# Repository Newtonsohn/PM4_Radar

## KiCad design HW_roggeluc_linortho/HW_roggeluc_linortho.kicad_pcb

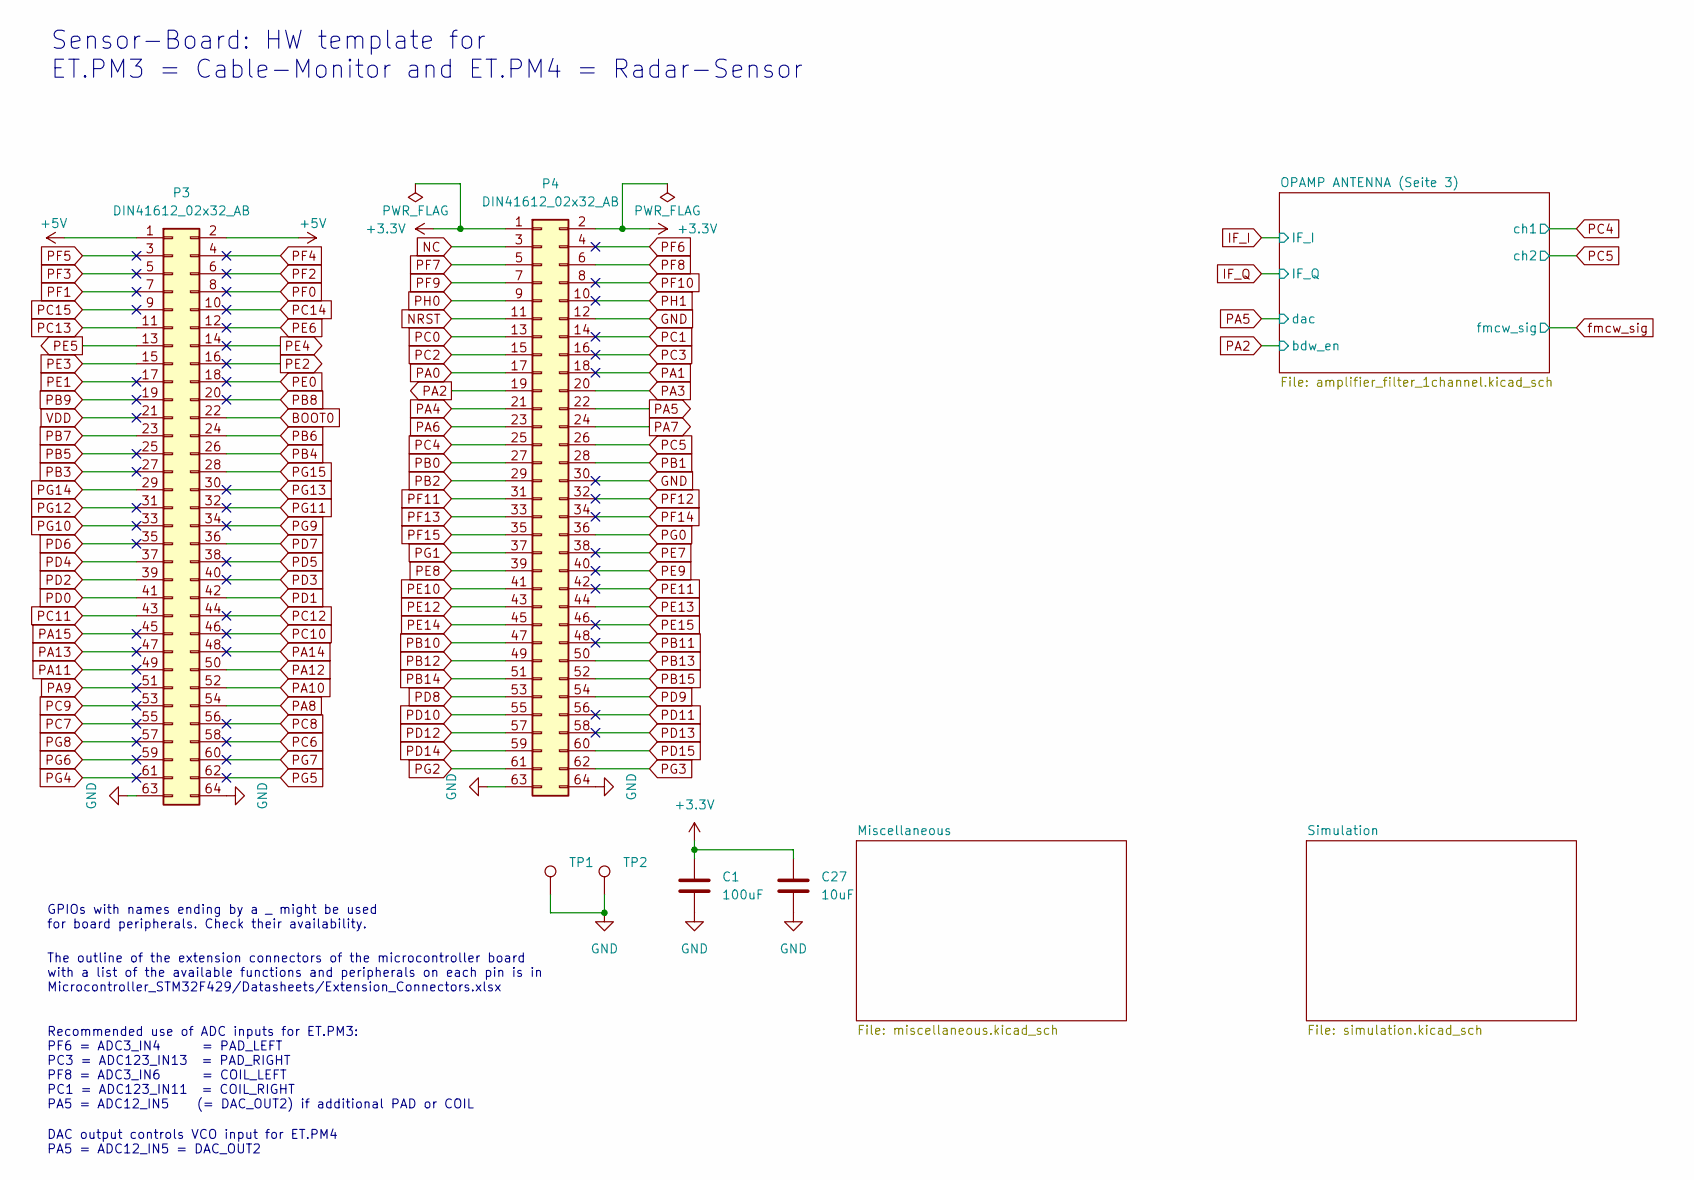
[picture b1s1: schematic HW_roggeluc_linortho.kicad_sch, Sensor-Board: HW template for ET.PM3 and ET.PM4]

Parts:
C1: 100uF; C_0805_2012Metric_Pad1.18x1.45mm_HandSolder
C27: 10uF; C_0805_2012Metric_Pad1.18x1.45mm_HandSolder
P3, P4: DIN41612_02x32_AB; PinSocket_2x32_P2.54mm_Vertical
TP1, TP2: TestPoint_Loop_D2.60mm_Drill1.6mm_Beaded

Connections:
+3.3V: C1.1, C27.1, P4.1 (Pin_a1), P4.2 (Pin_b1); also elsewhere on the board
+5V: P3.1 (Pin_a1), P3.2 (Pin_b1); also elsewhere on the board
BOOT0: P3.22 (Pin_b11)
Enable: P3.27 (Pin_a14); also elsewhere on the board
GND: C1.2, C27.2, P3.63 (Pin_a32), P3.64 (Pin_b32), P4.12 (Pin_b6), P4.30 (Pin_b15), P4.63 (Pin_a32), P4.64 (Pin_b32), TP1.1, TP2.1; also elsewhere on the board
LED_ON: P3.51 (Pin_a26); also elsewhere on the board
NC: P4.3 (Pin_a2)
NRST: P4.11 (Pin_a6)
PA0: P4.17 (Pin_a9)
PA1: P4.18 (Pin_b9)
PA2: P4.19 (Pin_a10); also elsewhere on the board
PA3: P4.20 (Pin_b10)
PA4: P4.21 (Pin_a11)
PA5: P4.22 (Pin_b11); also elsewhere on the board
PA6: P4.23 (Pin_a12); also elsewhere on the board
PA7: P4.24 (Pin_b12)
PA8: P3.54 (Pin_b27); also elsewhere on the board
PA10: P3.52 (Pin_b26)
PA11: P3.49 (Pin_a25)
PA12: P3.50 (Pin_b25)
PA13: P3.47 (Pin_a24)
PA14: P3.48 (Pin_b24)
PA15: P3.45 (Pin_a23)
PB0: P4.27 (Pin_a14)
PB1: P4.28 (Pin_b14)
PB2: P4.29 (Pin_a15)
PB4: P3.26 (Pin_b13)
PB5: P3.25 (Pin_a13)
PB6: P3.24 (Pin_b12)
PB7: P3.23 (Pin_a12)
PB8: P3.20 (Pin_b10)
PB9: P3.19 (Pin_a10)
PB10: P4.47 (Pin_a24)
PB11: P4.48 (Pin_b24)
PB12: P4.49 (Pin_a25)
PB13: P4.50 (Pin_b25)
PB14: P4.51 (Pin_a26)
PB15: P4.52 (Pin_b26)
PC0: P4.13 (Pin_a7)
PC1: P4.14 (Pin_b7)
PC2: P4.15 (Pin_a8)
PC3: P4.16 (Pin_b8)
PC4: P4.25 (Pin_a13); also elsewhere on the board
PC5: P4.26 (Pin_b13); also elsewhere on the board
PC6: P3.58 (Pin_b29)
PC7: P3.55 (Pin_a28)
PC8: P3.56 (Pin_b28)
PC9: P3.53 (Pin_a27)
PC10: P3.46 (Pin_b23)
PC11: P3.43 (Pin_a22)
PC12: P3.44 (Pin_b22)
PC13: P3.11 (Pin_a6)
PC14: P3.10 (Pin_b5)
PC15: P3.9 (Pin_a5)
PD0: P3.41 (Pin_a21)
PD1: P3.42 (Pin_b21)
PD2: P3.39 (Pin_a20)
PD3: P3.40 (Pin_b20)
PD4: P3.37 (Pin_a19)
PD5: P3.38 (Pin_b19)
PD6: P3.35 (Pin_a18)
PD7: P3.36 (Pin_b18)
PD8: P4.53 (Pin_a27)
PD9: P4.54 (Pin_b27)
PD10: P4.55 (Pin_a28)
PD11: P4.56 (Pin_b28)
PD12: P4.57 (Pin_a29)
PD13: P4.58 (Pin_b29)
PD14: P4.59 (Pin_a30)
PD15: P4.60 (Pin_b30)
PE0: P3.18 (Pin_b9)
PE1: P3.17 (Pin_a9)
PE2: P3.16 (Pin_b8); also elsewhere on the board
PE3: P3.15 (Pin_a8)
PE4: P3.14 (Pin_b7); also elsewhere on the board
PE5: P3.13 (Pin_a7); also elsewhere on the board
PE6: P3.12 (Pin_b6); also elsewhere on the board
PE7: P4.38 (Pin_b19)
PE8: P4.39 (Pin_a20)
PE9: P4.40 (Pin_b20)
PE10: P4.41 (Pin_a21)
PE11: P4.42 (Pin_b21)
PE12: P4.43 (Pin_a22)
PE13: P4.44 (Pin_b22)
PE14: P4.45 (Pin_a23)
PE15: P4.46 (Pin_b23)
PF0: P3.8 (Pin_b4)
PF1: P3.7 (Pin_a4)
PF2: P3.6 (Pin_b3)
PF3: P3.5 (Pin_a3)
PF4: P3.4 (Pin_b2)
PF5: P3.3 (Pin_a2)
PF6: P4.4 (Pin_b2)
PF7: P4.5 (Pin_a3)
PF8: P4.6 (Pin_b3)
PF9: P4.7 (Pin_a4)
PF10: P4.8 (Pin_b4)
PF11: P4.31 (Pin_a16)
PF12: P4.32 (Pin_b16)
PF13: P4.33 (Pin_a17)
PF14: P4.34 (Pin_b17)
PF15: P4.35 (Pin_a18)
PG0: P4.36 (Pin_b18)
PG1: P4.37 (Pin_a19)
PG2: P4.61 (Pin_a31)
PG3: P4.62 (Pin_b31)
PG4: P3.61 (Pin_a31)
PG5: P3.62 (Pin_b31)
PG6: P3.59 (Pin_a30)
PG7: P3.60 (Pin_b30)
PG8: P3.57 (Pin_a29)
PG9: P3.34 (Pin_b17)
PG10: P3.33 (Pin_a17)
PG11: P3.32 (Pin_b16)
PG12: P3.31 (Pin_a16)
PG13: P3.30 (Pin_b15)
PG14: P3.29 (Pin_a15)
PG15: P3.28 (Pin_b14)
PH0: P4.9 (Pin_a5)
PH1: P4.10 (Pin_b5)
VDD: P3.21 (Pin_a11)

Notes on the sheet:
The outline of the extension connectors of the microcontroller board with a list of the available functions and peripherals on each pin is in Microcontroller_STM32F429/Datasheets/Extension_Connectors.xlsx
DAC output controls VCO input for ET.PM4 PA5 = ADC12_IN5 = DAC_OUT2
GPIOs with names ending by a _ might be used for board peripherals. Check their availability.
Recommended use of ADC inputs for ET.PM3: PF6 = ADC3_IN4 = PAD_LEFT PC3 = ADC123_IN13 = PAD_RIGHT PF8 = ADC3_IN6 = COIL_LEFT PC1 = ADC123_IN11 = COIL_RIGHT PA5 = ADC12_IN5 (= DAC_OUT2) if additional PAD or COIL
Sensor-Board: HW template for ET.PM3 = Cable-Monitor and ET.PM4 = Radar-Sensor

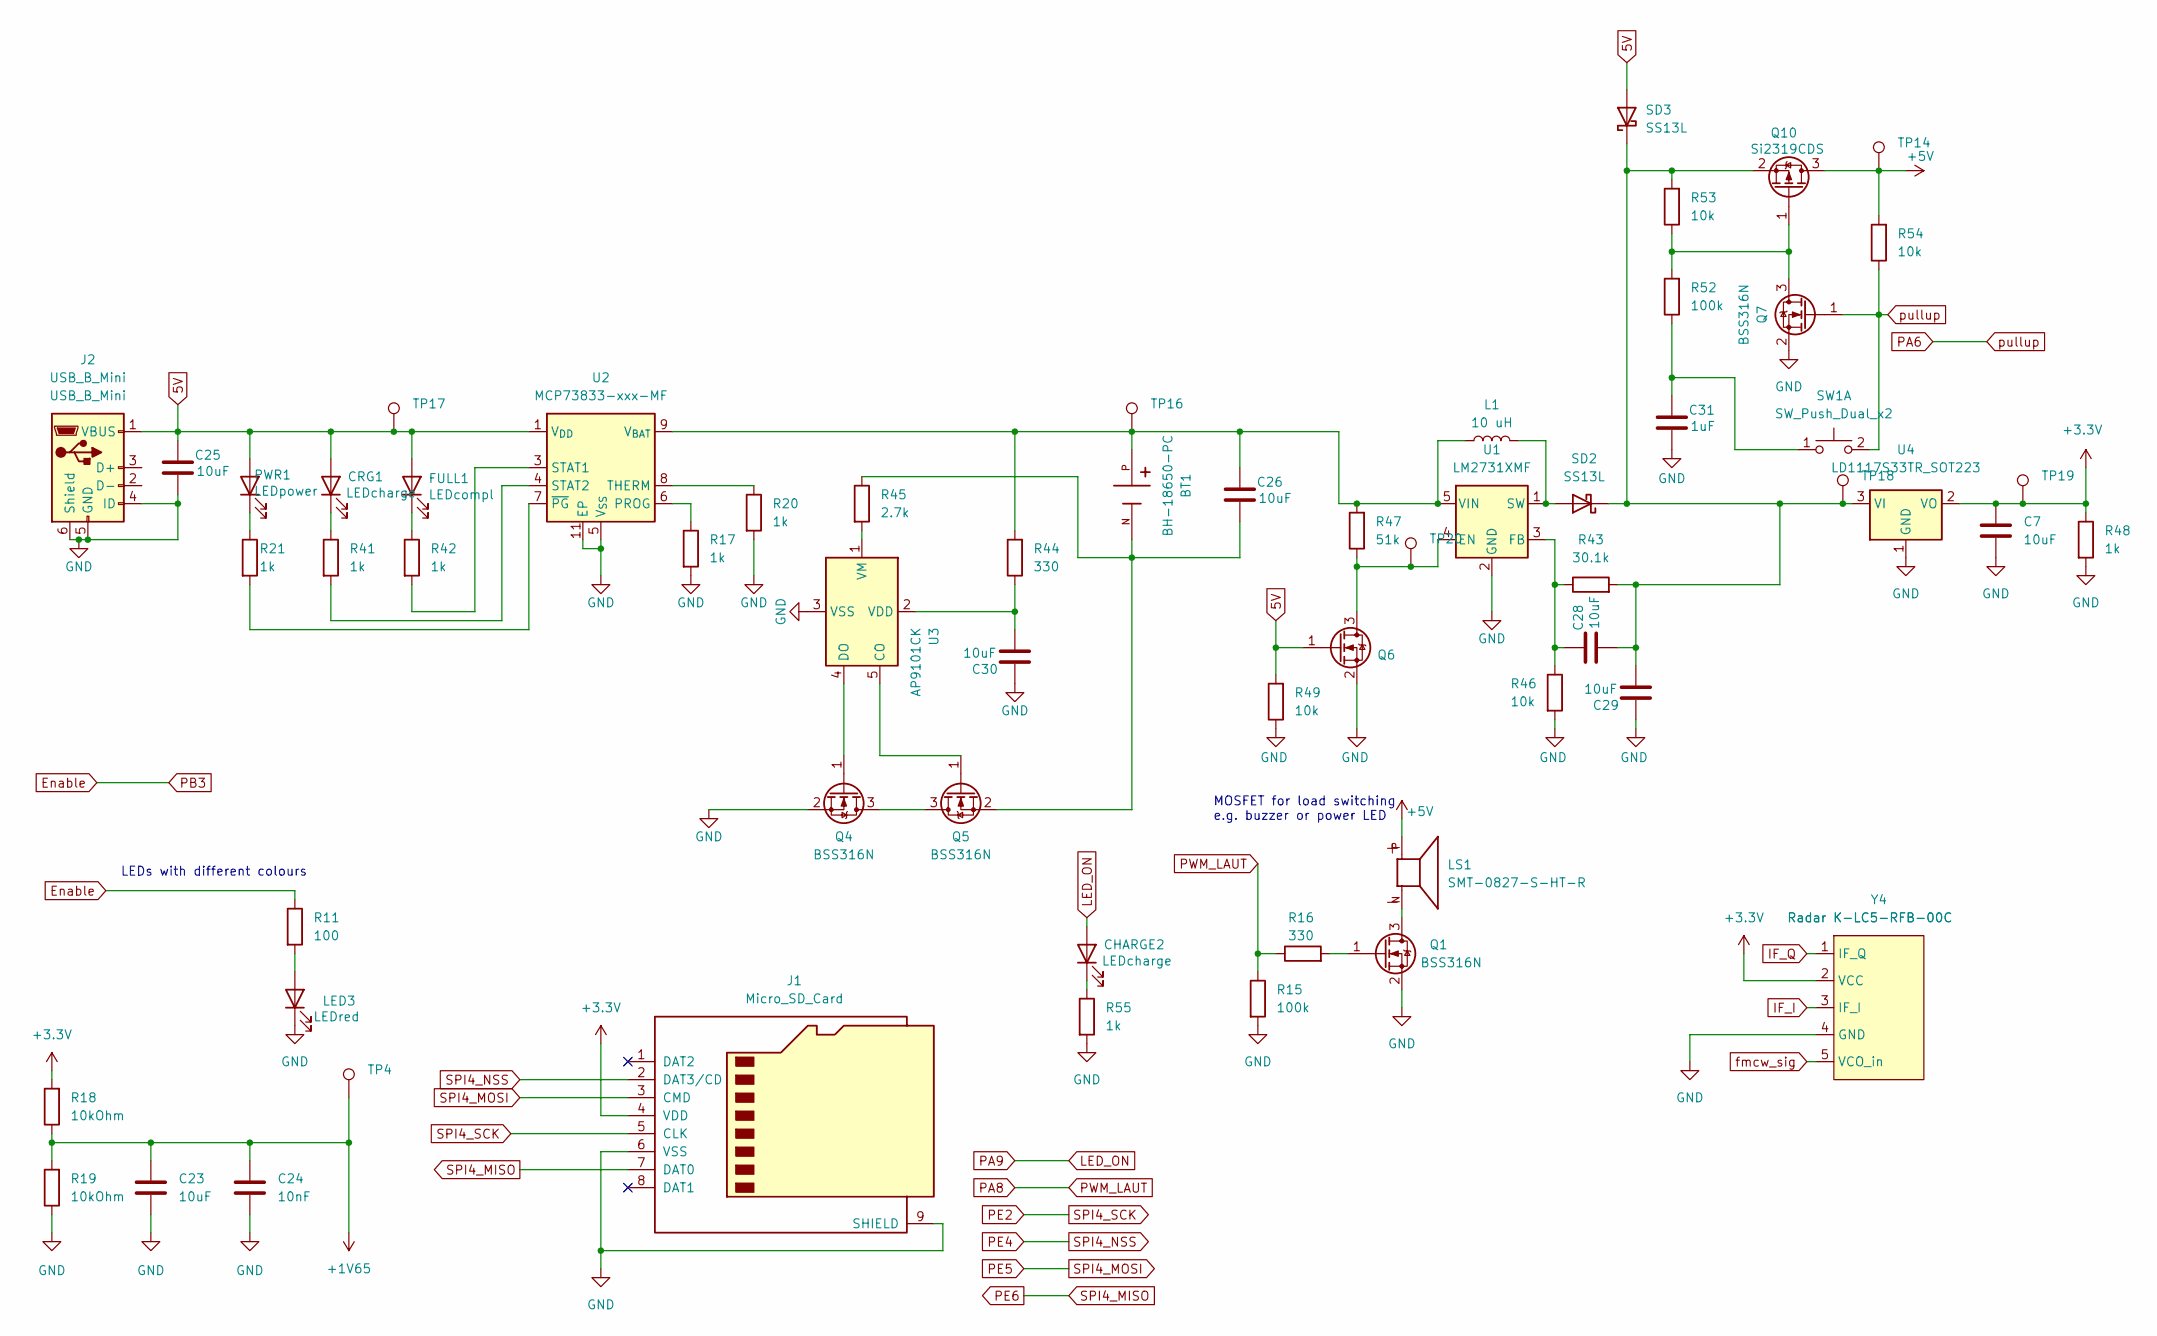
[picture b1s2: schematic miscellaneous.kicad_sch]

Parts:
BT1: BH-18650-PC; BAT_BH-18650-PC; PARTREV 05/17/19
C7, C23, C25, C26, C28, C29, C30: 10uF; C_0805_2012Metric_Pad1.18x1.45mm_HandSolder
C24: 10nF; C_0805_2012Metric_Pad1.18x1.45mm_HandSolder
C31: 1uF; C_0805_2012Metric_Pad1.18x1.45mm_HandSolder
CHARGE2: LEDcharge; LED_1206_3216Metric_Pad1.42x1.75mm_HandSolder
CRG1: LEDcharge; LED_1206_3216Metric_Pad1.42x1.75mm_HandSolder
FULL1: LEDcompl; LED_1206_3216Metric_Pad1.42x1.75mm_HandSolder
J1: Micro_SD_Card; microSD_HC_Wuerth_693072010801
J2: USB_B_Mini; USB_Mini-B_Lumberg_2486_01_Horizontal
L1: 10 uH; L_0805_2012Metric_Pad1.15x1.40mm_HandSolder
LED3: LEDred; LED_1206_3216Metric_Pad1.42x1.75mm_HandSolder
LS1: SMT-0827-S-HT-R; XDCR_SMT-0827-S-HT-R; PARTREV 31/03/20
PWR1: LEDpower; LED_1206_3216Metric_Pad1.42x1.75mm_HandSolder
Q1, Q4, Q5, Q6, Q7: BSS316N; SOT-23
Q10: Si2319CDS; SOT-23
R11: 100; R_0805_2012Metric_Pad1.20x1.40mm_HandSolder
R15, R52: 100k; R_0805_2012Metric_Pad1.20x1.40mm_HandSolder
R16, R44: 330; R_0805_2012Metric_Pad1.20x1.40mm_HandSolder
R17, R20, R21, R41, R42, R48, R55: 1k; R_0805_2012Metric_Pad1.20x1.40mm_HandSolder
R18, R19: 10kOhm; R_0805_2012Metric_Pad1.20x1.40mm_HandSolder
R43: 30.1k; R_0805_2012Metric_Pad1.20x1.40mm_HandSolder
R45: 2.7k; R_0805_2012Metric_Pad1.20x1.40mm_HandSolder
R46, R49, R53, R54: 10k; R_0805_2012Metric_Pad1.20x1.40mm_HandSolder
R47: 51k; R_0805_2012Metric_Pad1.20x1.40mm_HandSolder
SD2, SD3: SS13L; D_SMA
SW1: SW_Push_Dual_x2; SW_SPST_EVQQ2
TP4: TestPoint_Loop_D2.60mm_Drill1.6mm_Beaded
TP14, TP16, TP17, TP18, TP19, TP20: TestPoint_Loop_D2.60mm_Drill1.6mm_Beaded
U1: LM2731XMF; SOT-23-5
U2: MCP73833-xxx-MF; DFN-10-1EP_3x3mm_P0.5mm_EP1.58x2.35mm
U3: AP9101CK; SOT-23-5
U4: LD1117S33TR_SOT223; SOT-223-3_TabPin2
Y4: Radar K-LC5-RFB-00C; Radar_K-LC5

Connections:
5V: C25.1, CRG1.2 (A), FULL1.2 (A), J2.1 (VBUS), PWR1.2 (A), Q6.1 (G), R49.2, SD3.2 (A), TP17.1, U2.1 (V_{DD}), U2.2 (V_{DD})
+1V65: C23.1, C24.1, R18.1, R19.2, TP4.1; also elsewhere on the board
+3.3V: C7.1, J1.4 (VDD), R18.2, R48.1, TP19.1, U4.2 (VO), Y4.2 (VCC); also elsewhere on the board
+5V: LS1.P, Q10.3 (D), R54.2, TP14.1; also elsewhere on the board
Enable: R11.1; also elsewhere on the board
GND: C7.2, C23.2, C24.2, C25.2, C29.1, C30.1, C31.2, J1.6 (VSS), J1.9 (SHIELD), J2.4 (ID), J2.5 (GND), J2.6 (Shield), LED3.1 (K), Q1.2 (S), Q4.2 (S), Q6.2 (S), Q7.2 (S), R15.2, R17.2, R19.1, R20.2, R46.2, R48.2, R49.1, R55.2, U1.2 (GND), U2.5 (V_{SS}), U2.11 (EP), U3.3 (VSS), U4.1 (GND), Y4.4 (GND); also elsewhere on the board
IF_I: Y4.3 (IF_I); also elsewhere on the board
IF_Q: Y4.1 (IF_Q); also elsewhere on the board
LED_ON: CHARGE2.2 (A); also elsewhere on the board
unnamed: CHARGE2.1 (K), R55.1
unnamed: CRG1.1 (K), R41.1
unnamed: FULL1.1 (K), R42.1
unnamed: LED3.2 (A), R11.2
unnamed: PWR1.1 (K), R21.1
unnamed 21: LS1.N, Q1.3 (D); also elsewhere on the board
unnamed: Q1.1 (G), R16.2
unnamed: Q4.3 (D), Q5.3 (D)
unnamed: Q4.1 (G), U3.4 (DO)
unnamed: Q5.1 (G), U3.5 (CO)
unnamed: BT1.N, C26.2, Q5.2 (S), R45.1
unnamed: Q6.3 (D), R47.1, TP20.1, U1.4 (EN)
unnamed: Q7.3 (D), Q10.1 (G), R52.2, R53.1
unnamed: C28.2, C29.2, Q10.2 (S), R43.2, R53.2, SD2.1 (K), SD3.1 (K), TP18.1, U4.3 (VI)
unnamed: L1.2, SD2.2 (A), U1.1 (SW)
unnamed: C31.1, R52.1, SW1.1 (C)
unnamed: C28.1, R43.1, R46.1, U1.3 (FB)
unnamed: BT1.P, C26.1, L1.1, R44.2, R47.2, TP16.1, U1.5 (VIN), U2.9 (V_{BAT}), U2.10 (V_{BAT})
unnamed: R17.1, U2.6 (PROG)
unnamed: R42.2, U2.3 (STAT1)
unnamed: R41.2, U2.4 (STAT2)
unnamed: R20.1, U2.8 (THERM)
unnamed: R21.2, U2.7 (~PG)
unnamed: C30.2, R44.1, U3.2 (VDD)
unnamed: R45.2, U3.1 (VM)
PA6: Q7.1 (G), R54.1, SW1.2 (D); also elsewhere on the board
PA8: R15.1, R16.1; also elsewhere on the board
PE2: J1.5 (CLK); also elsewhere on the board
PE4: J1.2 (DAT3/CD); also elsewhere on the board
PE5: J1.3 (CMD); also elsewhere on the board
PE6: J1.7 (DAT0); also elsewhere on the board
fmcw_sig: Y4.5 (VCO_in); also elsewhere on the board

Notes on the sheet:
MOSFET for load switching e.g. buzzer or power LED
LEDs with different colours

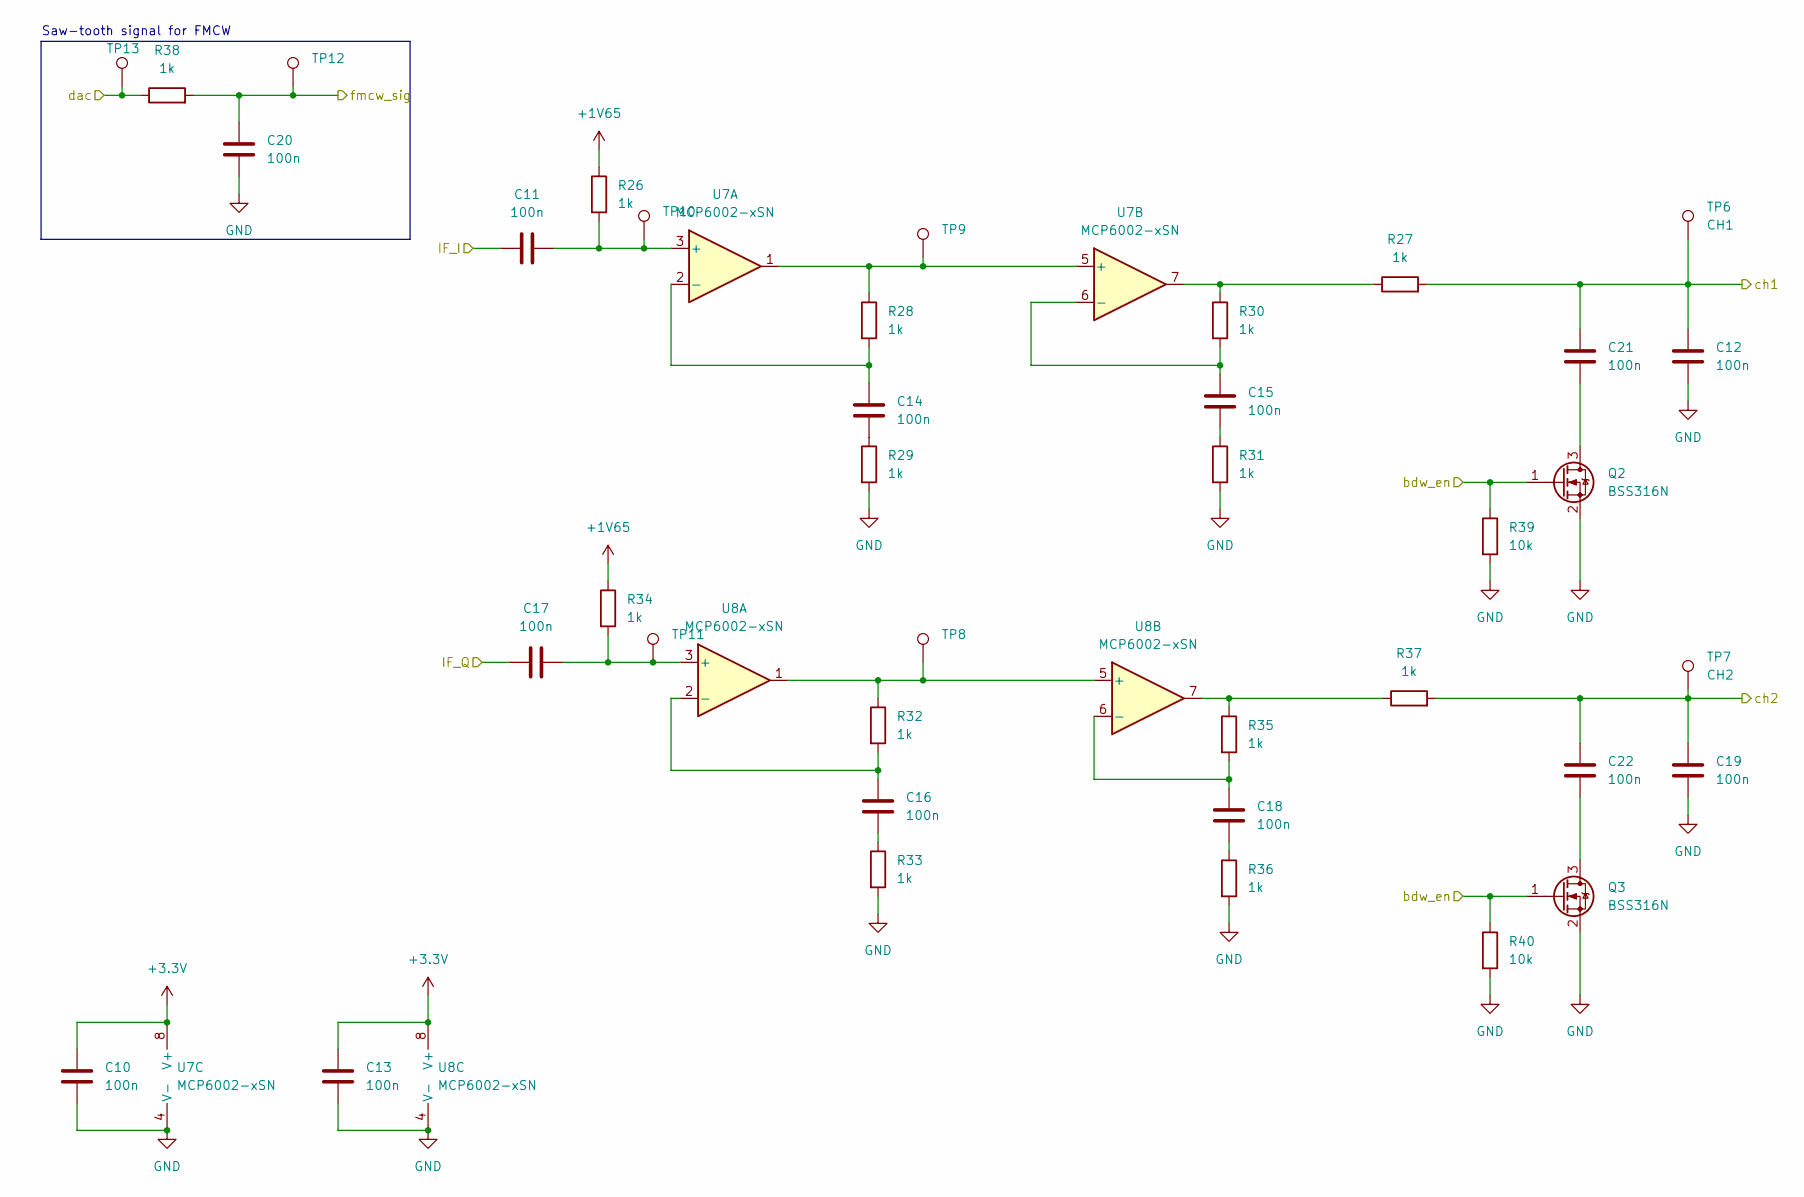
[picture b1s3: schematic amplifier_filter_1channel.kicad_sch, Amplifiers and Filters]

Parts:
C10, C11, C12, C13, C14, C15, C16, C17, C18, C19, C20, C21, C22: 100n; C_0805_2012Metric_Pad1.18x1.45mm_HandSolder
Q2, Q3: BSS316N; SOT-23
R26, R27, R28, R29, R30, R31, R32, R33, R34, R35, R36, R37, R38: 1k; R_0805_2012Metric_Pad1.20x1.40mm_HandSolder
R39, R40: 10k; R_0805_2012Metric_Pad1.20x1.40mm_HandSolder
TP6: CH1; TestPoint_Loop_D2.60mm_Drill1.6mm_Beaded
TP7: CH2; TestPoint_Loop_D2.60mm_Drill1.6mm_Beaded
TP8, TP9, TP10, TP11, TP12, TP13: TestPoint_Loop_D2.60mm_Drill1.6mm_Beaded
U7, U8: MCP6002-xSN; SOIC-8_3.9x4.9mm_P1.27mm

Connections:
+1V65: R26.1, R34.1; also elsewhere on the board
+3.3V: C10.1, C13.1, U7.8 (V+), U8.8 (V+); also elsewhere on the board
GND: C10.2, C12.1, C13.2, C19.1, C20.1, Q2.2 (S), Q3.2 (S), R29.2, R31.2, R33.2, R36.2, R39.2, R40.2, U7.4 (V-), U8.4 (V-); also elsewhere on the board
IF_I: C11.1; also elsewhere on the board
IF_Q: C17.1; also elsewhere on the board
unnamed: C14.1, R29.1
unnamed: C15.1, R31.1
unnamed: C16.1, R33.1
unnamed: C18.1, R36.1
unnamed: C21.1, Q2.3 (D)
unnamed: C22.1, Q3.3 (D)
unnamed: R27.1, R30.1, U7.7
unnamed: R35.1, R37.1, U8.7
unnamed: C11.2, R26.2, TP10.1, U7.3 (+)
unnamed: C14.2, R28.2, U7.2 (-)
unnamed: R28.1, TP9.1, U7.1, U7.5 (+)
unnamed: C15.2, R30.2, U7.6 (-)
unnamed: C17.2, R34.2, TP11.1, U8.3 (+)
unnamed: C16.2, R32.2, U8.2 (-)
unnamed: R32.1, TP8.1, U8.1, U8.5 (+)
unnamed: C18.2, R35.2, U8.6 (-)
PA2: Q2.1 (G), Q3.1 (G), R39.1, R40.1; also elsewhere on the board
PA5: R38.1, TP13.1; also elsewhere on the board
PC4: C12.2, C21.2, R27.2, TP6.1; also elsewhere on the board
PC5: C19.2, C22.2, R37.2, TP7.1; also elsewhere on the board
fmcw_sig: C20.2, R38.2, TP12.1; also elsewhere on the board

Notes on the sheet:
Saw-tooth signal for FMCW

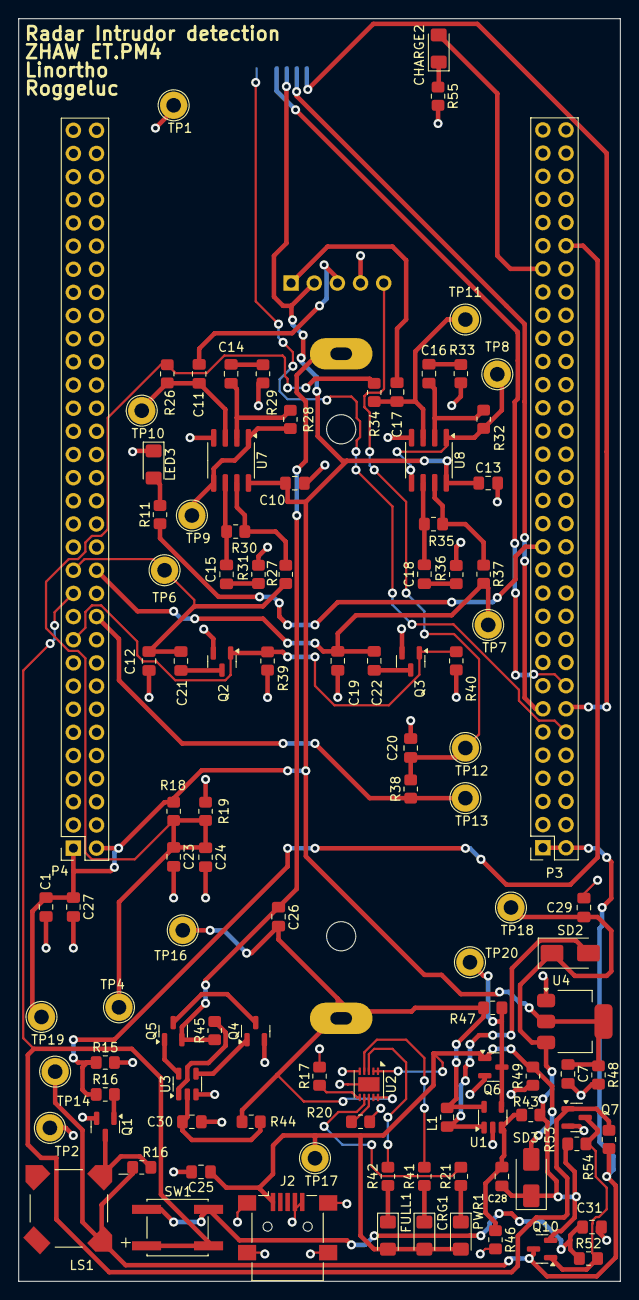
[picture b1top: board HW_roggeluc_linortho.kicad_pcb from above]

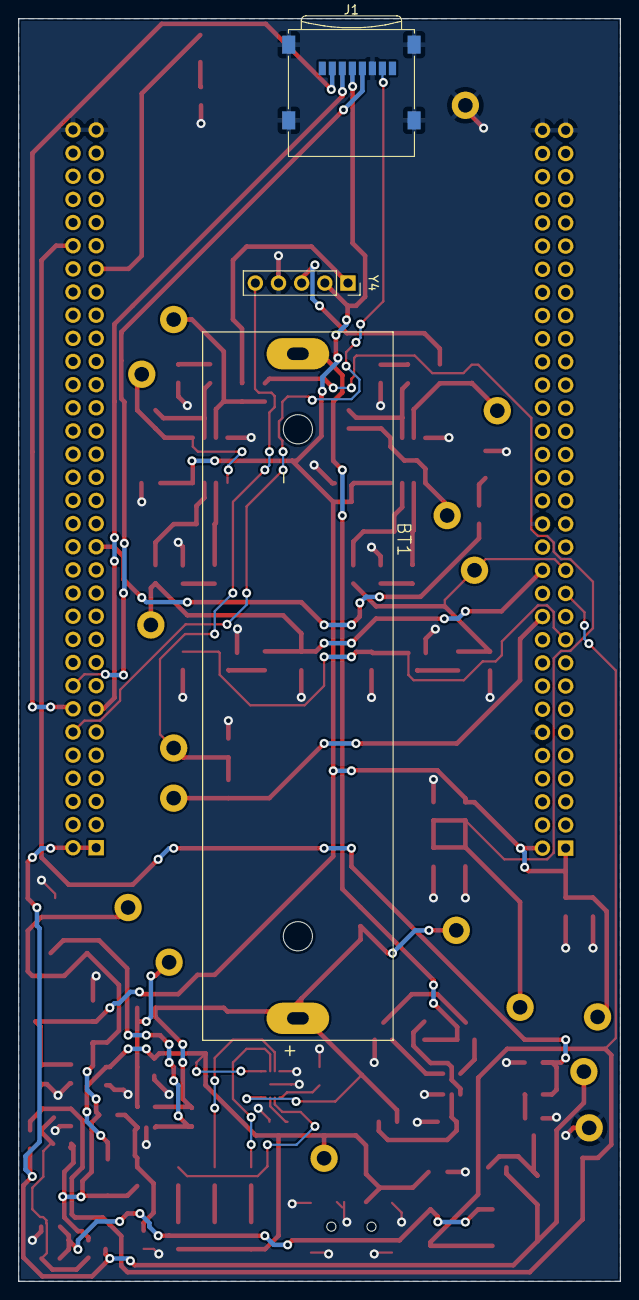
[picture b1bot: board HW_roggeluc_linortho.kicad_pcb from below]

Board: 2 copper layers, 66.0 x 138.5 mm, 108 parts (3 on the bottom side), 61 nets.

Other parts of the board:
R16#2: 10; R_0805_2012Metric_Pad1.20x1.40mm_HandSolder

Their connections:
+5V: R16#2.1; also elsewhere on the board
unnamed 21: R16#2.2; also elsewhere on the board

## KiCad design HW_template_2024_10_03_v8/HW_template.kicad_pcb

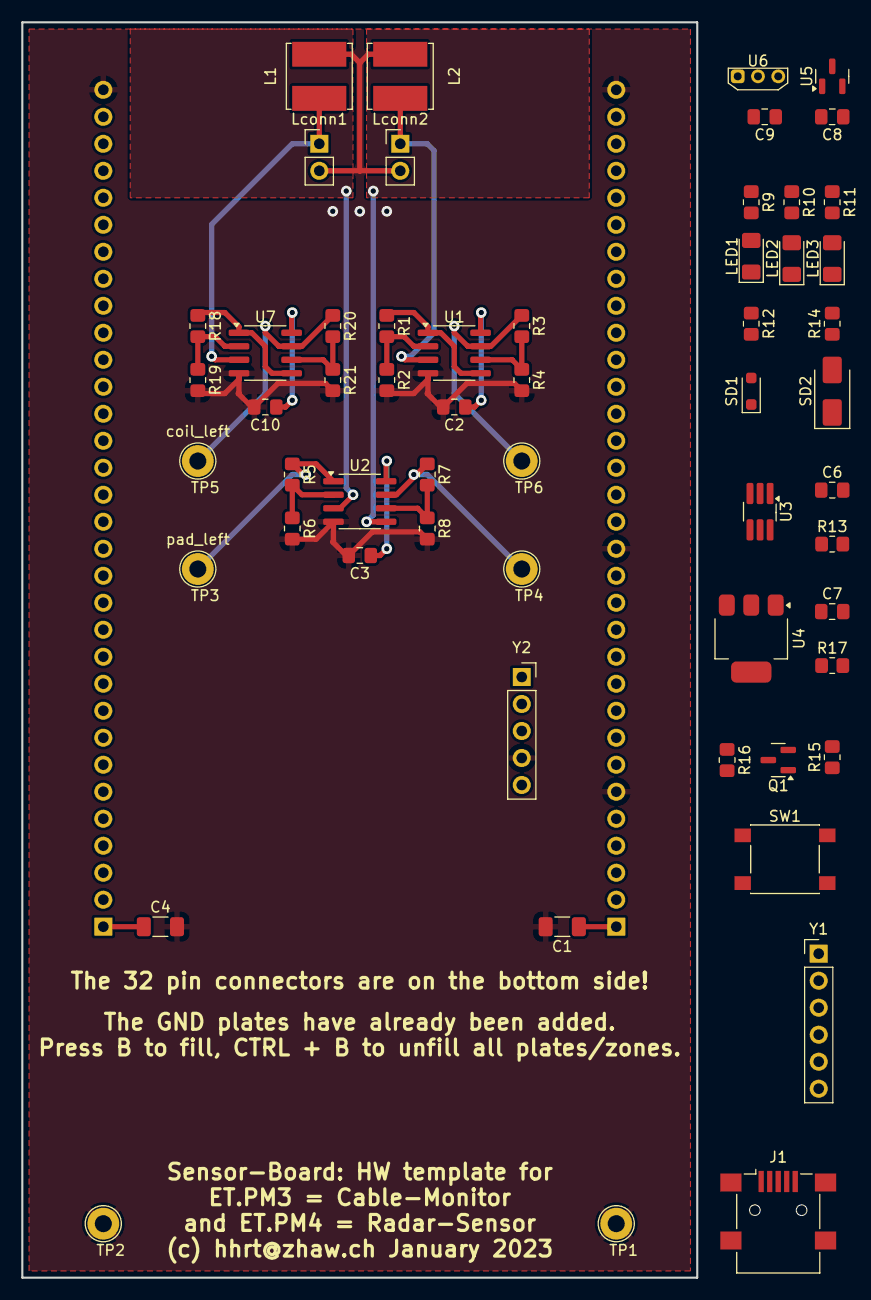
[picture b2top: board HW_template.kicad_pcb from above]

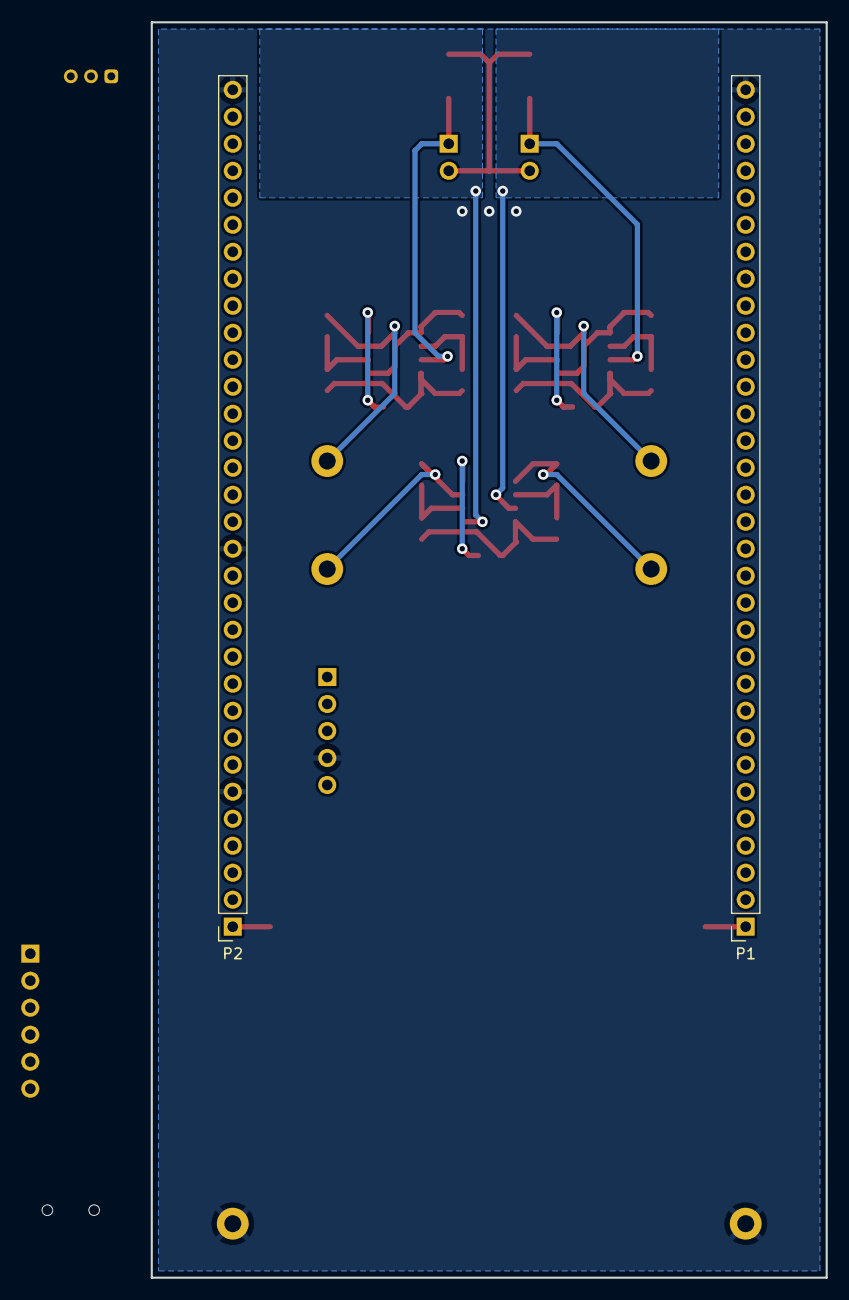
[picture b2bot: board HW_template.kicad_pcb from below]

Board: 2 copper layers, 63.5 x 118.1 mm, 59 parts (2 on the bottom side), 27 nets.

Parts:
C1, C4: 100uF; C_1206_3216Metric_Pad1.33x1.80mm_HandSolder
C2, C3, C10: 100n; C_0805_2012Metric_Pad1.18x1.45mm_HandSolder
C6, C7: 10uF; C_0805_2012Metric_Pad1.18x1.45mm_HandSolder
C8, C9: 100nF; C_0805_2012Metric_Pad1.18x1.45mm_HandSolder
J1: USB_B_Mini; USB_Mini-B_Lumberg_2486_01_Horizontal
L1, L2: 15mH; L_Bourns_SRN6045TA
LED1: LEDblue; LED_1206_3216Metric_Pad1.42x1.75mm_HandSolder
LED2: LEDgreen; LED_1206_3216Metric_Pad1.42x1.75mm_HandSolder
LED3: LEDred; LED_1206_3216Metric_Pad1.42x1.75mm_HandSolder
Lconn1, Lconn2: Conn_01x02_Male; PinHeader_1x02_P2.54mm_Vertical
P1, P2: type="R" model="Conn_01x32_Female" lib=""; PinSocket_1x32_P2.54mm_Vertical
Q1: BSS316N; SOT-23
R1, R18: 10k; R_0805_2012Metric_Pad1.20x1.40mm_HandSolder
R2, R4, R6, R8, R13, R17, R19, R21: 1k; R_0805_2012Metric_Pad1.20x1.40mm_HandSolder
R3, R20: 12k; R_0805_2012Metric_Pad1.20x1.40mm_HandSolder
R5: 220k; R_0805_2012Metric_Pad1.20x1.40mm_HandSolder
R7, R15: 100k; R_0805_2012Metric_Pad1.20x1.40mm_HandSolder
R9: 22; R_0805_2012Metric_Pad1.20x1.40mm_HandSolder
R10: 47; R_0805_2012Metric_Pad1.20x1.40mm_HandSolder
R11, R12, R14: 100; R_0805_2012Metric_Pad1.20x1.40mm_HandSolder
R16: 10; R_0805_2012Metric_Pad1.20x1.40mm_HandSolder
SD1: SD103AWS; D_SOD-323_HandSoldering
SD2: SS13L; D_SMA
SW1: type="R" model="SW_Push" lib=""; SW_SPST_PTS645
TP1, TP2, TP4, TP6: TestPoint_Loop_D2.60mm_Drill1.6mm_Beaded
TP3: pad_left; TestPoint_Loop_D2.60mm_Drill1.6mm_Beaded
TP5: coil_left; TestPoint_Loop_D2.60mm_Drill1.6mm_Beaded
U1, U2, U7: MCP6002-xSN; SOIC-8_3.9x4.9mm_P1.27mm
U3: SiP32508; TSOT-23-6_HandSoldering
U4: LD1117S33TR_SOT223; SOT-223-3_TabPin2
U5: type="R" model="DRV5053_SMD" lib=""; SOT-23
U6: type="R" model="DRV5053_THT" lib=""; TO-92Flat_wide
Y1: OpenLog; PinHeader_1x06_P2.54mm_Vertical
Y2: Radar K-LC5-RFB-00C; Radar_K-LC5

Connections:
+3V0: C1.1, C2.1, C3.1, C8.2, C9.2, C10.1, P2.1, U1.8 (V+), U2.8 (V+), U5.1 (VCC), U6.1 (VCC), U7.8 (V+), Y2.2 (VCC)
+5V: C4.1, P1.1, R16.1, U3.5 (IN), U3.6 (IN), Y1.4 (VCC)
Enable: Q1.1 (G), R9.1, R10.1, R11.1, R12.1, R14.1, R15.1, U3.3 (EN)
GND: C1.2, C2.2, C3.2, C4.2, C6.2, C7.2, C8.1, C9.1, C10.2, J1.5 (GND), J1.6 (Shield), L1.2, L2.2, LED1.1 (K), LED2.1 (K), LED3.1 (K), Lconn1.2, Lconn2.2, P1.32, P2.6, P2.15, P2.32, Q1.2 (S), R2.2, R4.2, R6.2, R8.2, R13.2, R15.2, R17.2, R19.2, R21.2, SD1.1 (K), SD2.1 (K), TP1.1, TP2.1, U1.4 (V-), U2.4 (V-), U3.4 (GND), U4.1 (GND), U5.3 (GND), U6.2 (GND), U7.4 (V-), Y1.5 (GND), Y1.6 (BLK), Y2.4 (GND)
unnamed: LED1.2 (A), R9.2
unnamed: LED2.2 (A), R10.2
unnamed: LED3.2 (A), R11.2
unnamed: Q1.3 (D), R16.2
unnamed: R12.2, SD1.2 (A)
unnamed: R14.2, SD2.2 (A)
unnamed: R1.2, R2.1, U1.2 (-)
unnamed: R1.1, U1.1, U1.5 (+)
unnamed: R3.2, R4.1, U1.6 (-)
unnamed: R5.2, R6.1, U2.2 (-)
unnamed: R7.2, R8.1, U2.6 (-)
unnamed: C6.1, R13.1, U3.1 (OUT), U3.2 (OUT), U4.3 (VI)
unnamed: C7.1, R17.1, U4.2 (VO)
unnamed: R18.2, R19.1, U7.2 (-)
unnamed: R18.1, U7.1, U7.5 (+)
unnamed: R20.2, R21.1, U7.6 (-)
PA5: P2.11, Y2.5 (VCO_in)
PC1_: P2.7, R3.1, TP6.1, U1.7
PC3: P2.8, R7.1, TP4.1, U2.7
PF6: P2.2, R5.1, TP3.1, U2.1
PF8_: P2.3, R20.1, TP5.1, U7.7
coil_left: L1.1, Lconn1.1, U7.3 (+)
coil_right: L2.1, Lconn2.1, U1.3 (+)

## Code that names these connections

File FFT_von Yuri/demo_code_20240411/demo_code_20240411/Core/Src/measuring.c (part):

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 * @brief Configure GPIOs in analog mode.
 *
 * @note The input number for the ADCs is not equal to the GPIO pin number!
 * - ADC3_IN4 = GPIO PF6
 * - ADC123_IN13 = GPIO PC3
 * - ADC12_IN5 = GPIO PA5
 * - DAC_OUT2 = GPIO PA5 (= same GPIO as ADC12_IN5)
 *****************************************************************************/
void MEAS_GPIO_analog_init(void)
{

	__HAL_RCC_GPIOF_CLK_ENABLE();		// Enable Clock for GPIO port F
	GPIOF->MODER |= (3UL << GPIO_MODER_MODER6_Pos);	// Analog PF6 = ADC3_IN4
	__HAL_RCC_GPIOC_CLK_ENABLE();		// Enable Clock for GPIO port C
	GPIOC->MODER |= (3UL << GPIO_MODER_MODER3_Pos);	// Analog PC3 = ADC123_IN13
	__HAL_RCC_GPIOA_CLK_ENABLE();		// Enable Clock for GPIO port A
	GPIOA->MODER |= (3UL << GPIO_MODER_MODER5_Pos);	// Analog PA5 ADC12_IN5
    __HAL_RCC_GPIOC_CLK_ENABLE();
    // Für ADC1_IN14 (PC4) und ADC2_IN15 (PC5)
    GPIOC->MODER |= (3UL << GPIO_MODER_MODER4_Pos) | (3UL << GPIO_MODER_MODER5_Pos);

}
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/** ***************************************************************************
 * @brief Initialize the DAC
 *
 * The output used is DAC_OUT2 = GPIO PA5
 * @n As DAC_OUT2 = GPIO PA5 (= same GPIO as ADC12_IN5)
 * it is possible to monitor the output voltage DAC_OUT2 by the input ADC12_IN5.
 *****************************************************************************/
void DAC_init(void)
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/** ***************************************************************************
 * @brief Initialize the ADC in single conversion mode
 *
 * The input is ADC3_IN4 = GPIO PF6
 *****************************************************************************/
void ADC3_IN4_single_init(void)
{
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 * The ADC3 trigger is set to TIM2 TRGO event
 * and the timer starts the ADC directly without CPU intervention.
 * @n The ADC is configured for end of conversion interrupt.
 * @n The input is ADC3_IN4 = GPIO PF6
 *****************************************************************************/
void ADC3_IN4_timer_init(void)
{
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 * @ The ADC3 triggers the DMA2_Stream1 to transfer the new data directly
 * to memory without CPU intervention.
 * @n The DMA triggers the transfer complete interrupt when all data is ready.
 * @n The input is ADC3_IN4 = GPIO PF6
 *****************************************************************************/
void ADC3_IN4_DMA_init(void)
{
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 * @n The ADC1 triggers the DMA2_Stream4 to transfer the new data directly
 * to memory without CPU intervention.
 * @n The DMA triggers the transfer complete interrupt when all data is ready.
 * @n The input used with ADC1 is ADC123_IN13 = GPIO PC3
 * @n The input used with ADC2 is ADC12_IN5 = GPIO PA5
 *****************************************************************************/
void ADC1_IN13_ADC2_IN5_dual_init(void)
{
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 * and transfered to memory by the DMA.
 * @n As each conversion triggers the DMA, the number of transfers is doubled.
 * @n The DMA triggers the transfer complete interrupt when all data is ready.
 * @n The inputs used are ADC123_IN13 = GPIO PC3 and ADC12_IN5 = GPIO PA5
 *****************************************************************************/
void ADC2_IN13_IN5_scan_init(void)
{
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 * and transfered to memory by the DMA.
 * @n As each conversion triggers the DMA, the number of transfers is doubled.
 * @n The DMA triggers the transfer complete interrupt when all data is ready.
 * @n The inputs used are ADC123_IN13 = GPIO PC3 and ADC3_IN4 = GPIO PF6
 *****************************************************************************/
void ADC3_IN13_IN4_scan_init(void)
{
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
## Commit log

2025-03-07 Renane to HW_roggeluc_linortho
2025-03-07 error renaming
2025-03-07 NEW CLEAN COMMIT WITH CORRECT NAME
2025-03-07 OPAMP ANTENNA
2025-03-24 Hoi Lucas
2025-03-30 adasdasd
2025-03-31 PCB ORDERED
2025-04-06 kkkkjjj
2025-04-11 figdilucashihi
2025-04-11 figdiimmernohihi
2025-04-18 werteOPAMP
2025-04-18 wydxgh
2025-05-02 dobler helpout
2025-05-08 FICKDIESESCHEISSEICHHASSEZHAW
2025-05-16 Neue SW von Yuri
